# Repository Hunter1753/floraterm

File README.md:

# FloraTerm

a portable linux terminal

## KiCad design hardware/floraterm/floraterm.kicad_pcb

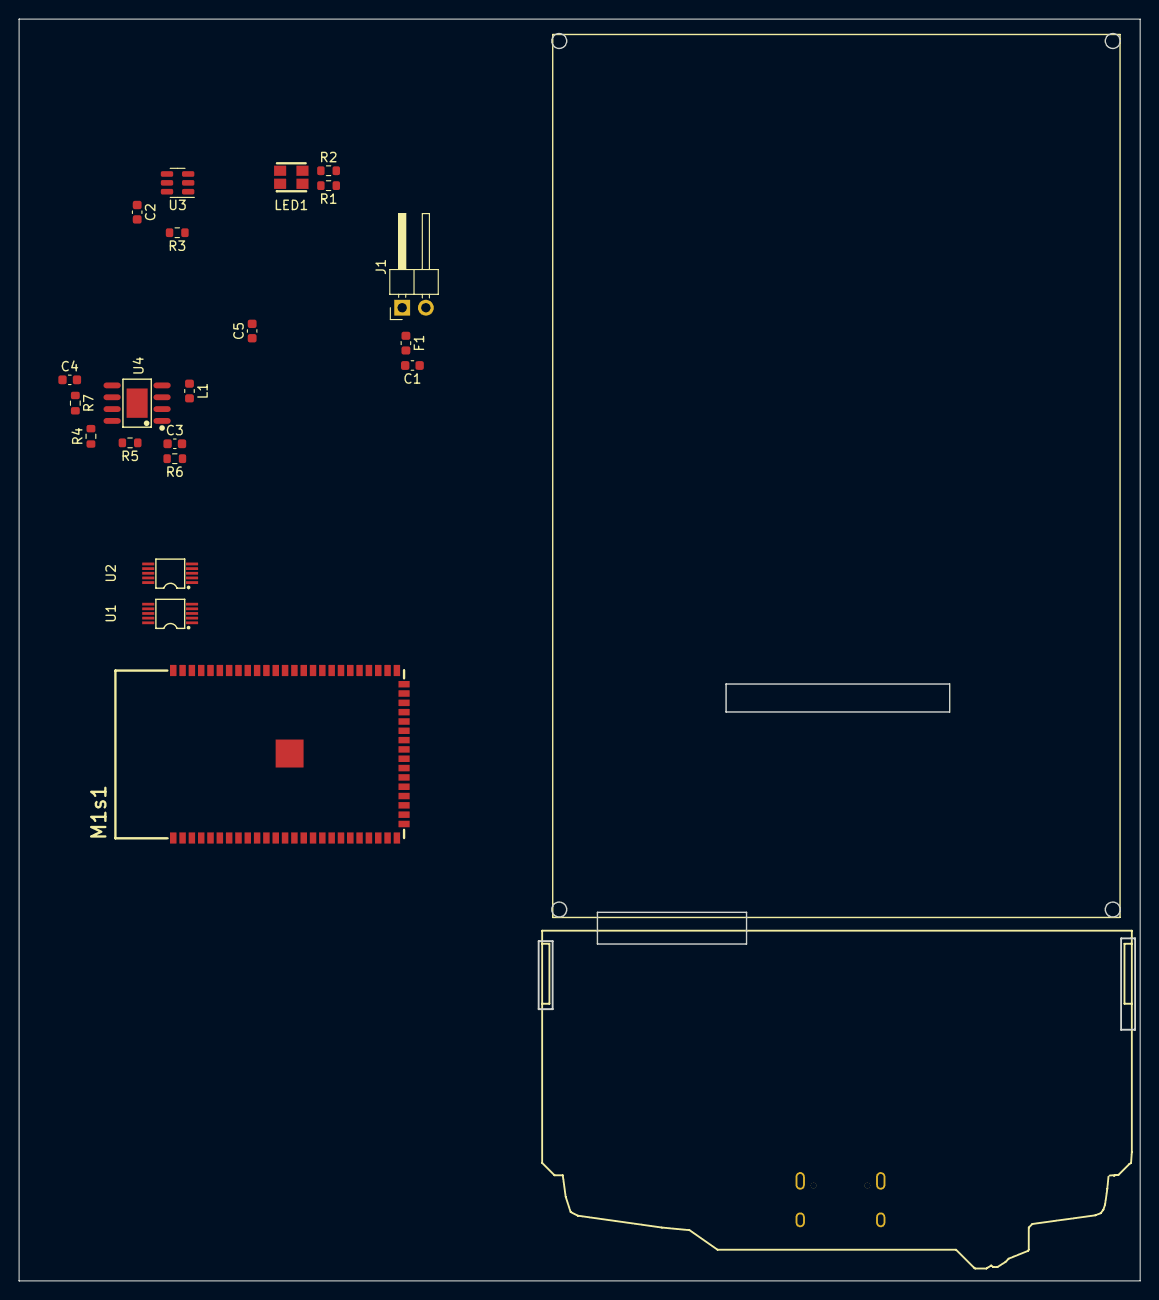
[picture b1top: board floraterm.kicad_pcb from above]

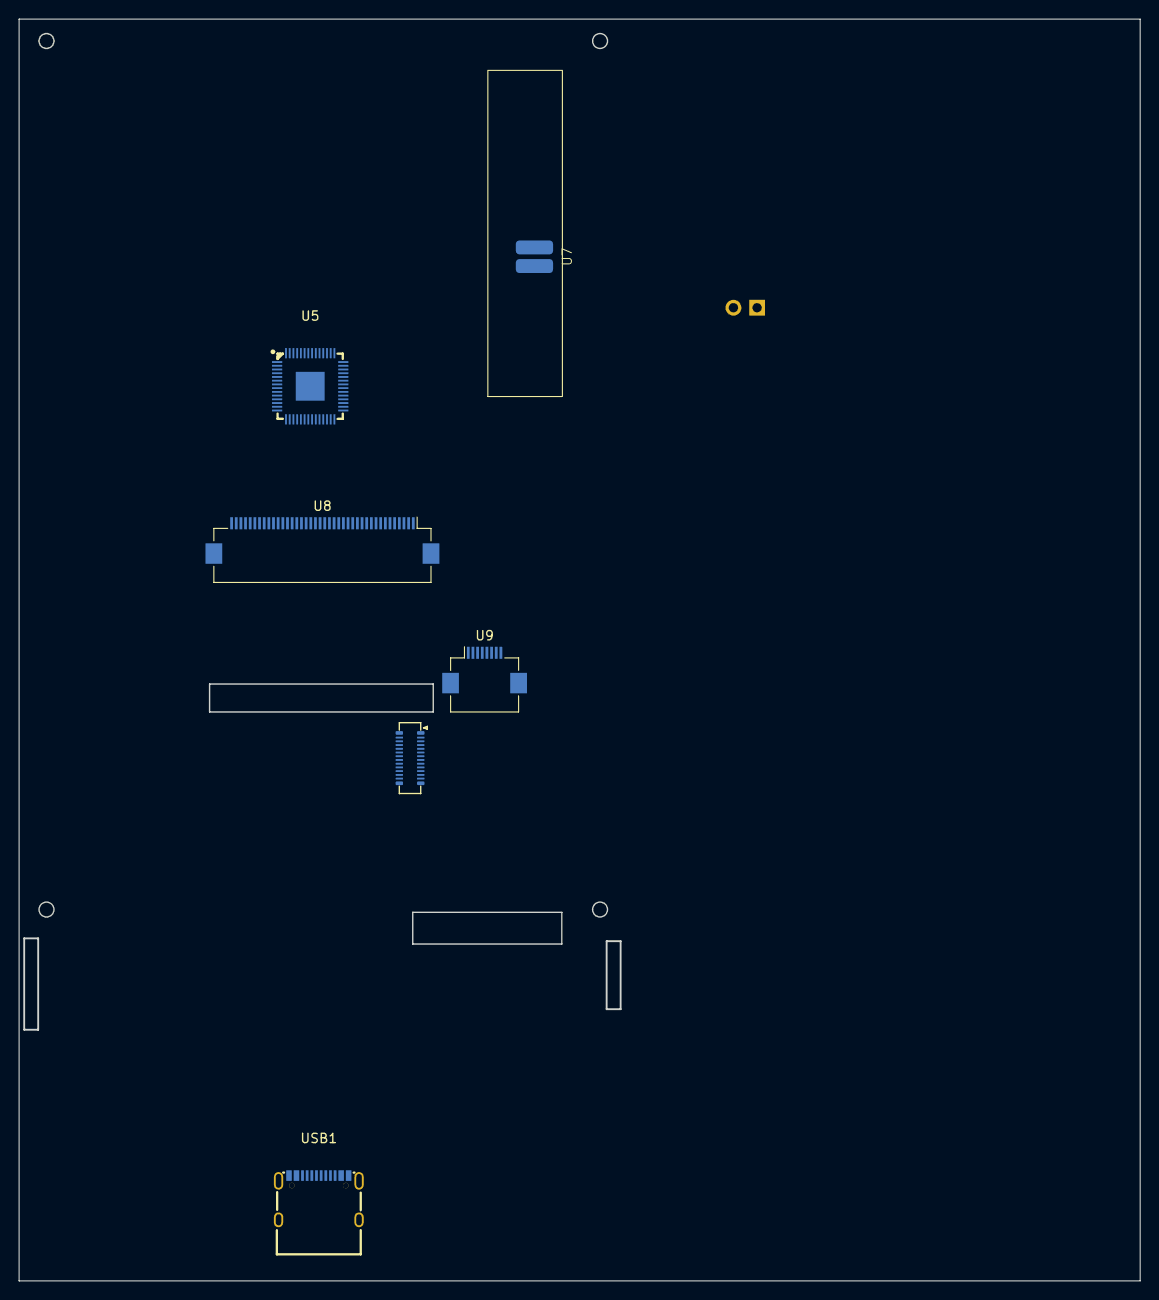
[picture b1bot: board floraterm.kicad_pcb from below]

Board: 2 copper layers, 120.3 x 135.4 mm, 27 parts (6 on the bottom side), 17 nets, no tracks yet.

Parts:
C1, C2: 10uF; C_0603_1608Metric
C3: 1.5nF; C_0603_1608Metric
C4: 0.1uF; C_0603_1608Metric
C5: 22uF; C_0603_1608Metric
F1: 800mA; Fuse_0603_1608Metric
J1: Conn_01x02_Pin; PinHeader_1x02_P2.54mm_Horizontal
L1: 10uH; L_0603_1608Metric
LED1: E6C1209SEQBC2UDA; LED-ARRAY-SMD_4P-L3.2-W2.7_E6C1209SEQBC2UDA
M1s1: 0_M1s; M1s
R1, R2: 1k; R_0603_1608Metric
R3: 2.5k; R_0603_1608Metric
R4: 340k; R_0603_1608Metric
R5: 200k; R_0603_1608Metric
R6: 15k; R_0603_1608Metric
R7: 1M; R_0603_1608Metric
U1, U2: TMUX1104DGSR; VSSOP-10_L3.0-W3.0-P0.50-LS4.9-BL
U3: LGS4084HB6; SOT-23-6
U4: TX4401; ESOP-8_L4.9-W3.9-P1.27-LS6.0-BL-EP-2
U5: RP2040; LQFN-56_L7.0-W7.0-P0.4-EP
U6: BBQ10KBD; BM14B(0.8)-24DS-0.4V(53)
U7: iPhone 13 PM SPK; iphone_13_pro_max
U8: ILI9488; Hirose_FH12-40S-0.5SH_1x40-1MP_P0.50mm_Horizontal
U9: GT911; Hirose_FH12-8S-0.5SH_1x08-1MP_P0.50mm_Horizontal
USB1: GT-USB-7004; USB-C-SMD_GT-USB-7004

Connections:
+BATT: C1.2, F1.2, R7.1, U3.3 (BAT), U4.6 (VIN)
-BATT: C1.1, C2.2, C4.2, C5.2, J1.2, R3.1, R5.1, U3.2 (GND), U4.9 (GND), USB1.1 (SHELL), USB1.2 (SHELL), USB1.3 (SHELL), USB1.4 (SHELL), USB1.A1B12 (GND), USB1.B1A12 (GND)
/power_management/3v3: C5.1, R4.2, U4.5 (VOUT)
/power_management/DC-DC_EN^{(pull to GND to activate)}: C4.1, R7.2, U4.7 (EN)
unnamed: C3.2, R6.1
unnamed: F1.1, J1.1
unnamed: LED1.1 (+), R1.2
unnamed: LED1.3 (+), R2.1
unnamed: LED1.4 (-), U3.1 (CHRG)
unnamed: LED1.2 (-), U3.5 (FULL)
unnamed: R3.2, U3.6 (PROG)
unnamed: R4.1, R5.2, R6.2, U4.8 (FB)
unnamed: L1.2, U4.3 (SW1)
unnamed: L1.1, U4.4 (SW2)
unnamed: C3.1, U4.1 (VC)
unnamed: U6.1 (GND), U6.5 (GND), U6.11 (GND), U6.12 (GND), U6.13 (GND), U6.14 (GND), U6.15 (GND), U6.16 (GND), U6.28 (GND)
VBUS_USB: C2.1, R1.1, R2.2, U3.4 (VCC), USB1.A4B9 (VBUS), USB1.B4A9 (VBUS)

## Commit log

2023-11-16 add initial components
2023-11-21 add dcdc and bat chrg
2023-11-28 add rp2040
2023-11-29 add screen, keyboard and speaker
